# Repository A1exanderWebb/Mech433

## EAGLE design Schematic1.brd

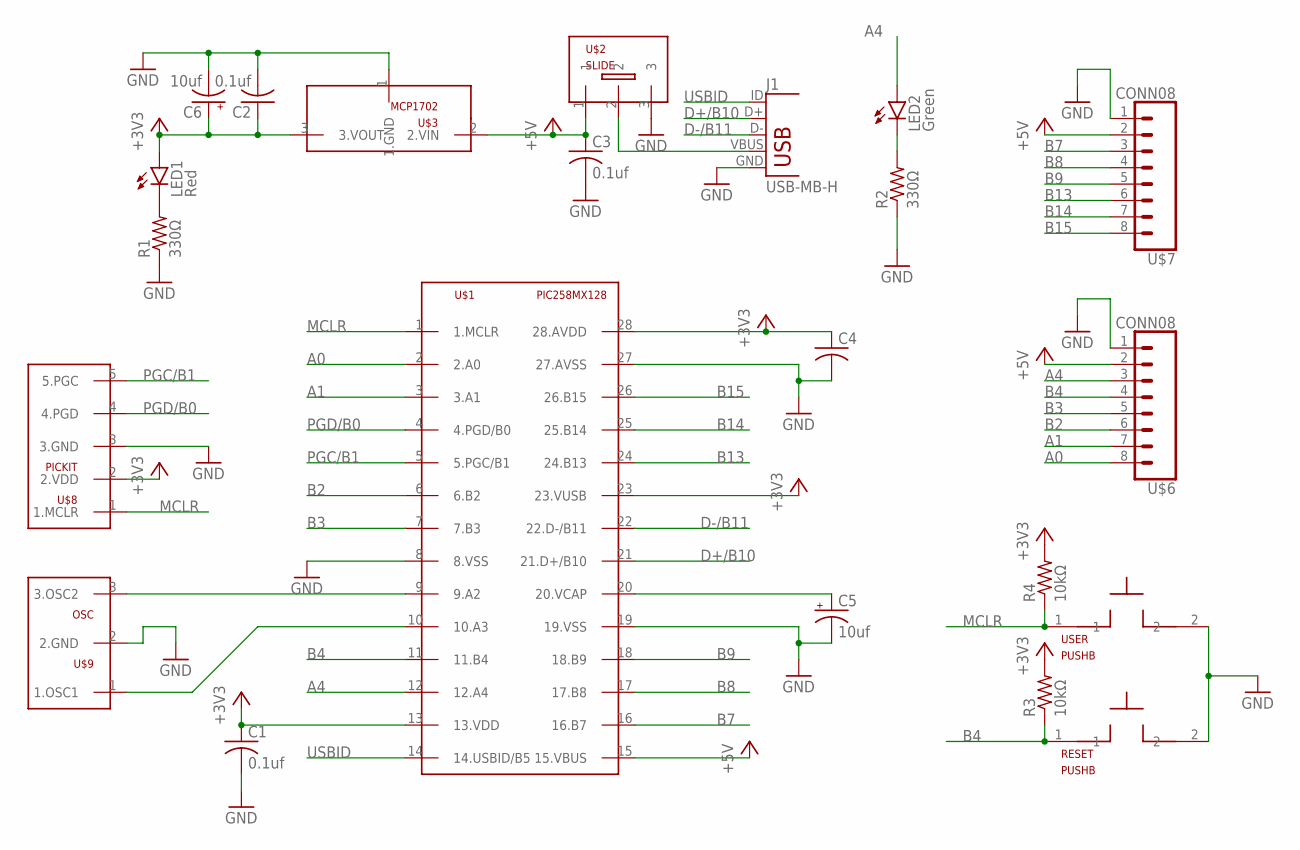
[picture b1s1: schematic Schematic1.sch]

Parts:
C1, C2, C3: 0.1uf; C025-025X050
C4: C-US025-025X050; C025-025X050
C5, C6: 10uf; B45181B
J1: USB-MB-H
LED1: Red; LED3MM
LED2: Green; LED3MM
R1, R2: 330Ω; 0207/10
R3, R4: 10kΩ; 0207/10
RESET: PUSHB
U$1: PIC258MX128; DIL28-3
U$2: SLIDE
U$3: MCP1702; TO92
U$6, U$7: CONN08; 1X08
U$8: PICKIT; 1X05
U$9: OSC
USER: PUSHB

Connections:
+3V3: C1.1, C2.1, C4.1, C6.+, LED1.A, R3.2, R4.2, U$1.13 (13.VDD), U$1.23 (23.VUSB), U$1.28 (28.AVDD), U$3.3 (3.VOUT), U$8.2 (2.VDD)
+5V: C3.1, U$1.15 (15.VBUS), U$2.1, U$3.2 (2.VIN), U$6.2, U$7.2
A0: U$1.2 (2.A0), U$6.8
A1: U$1.3 (3.A1), U$6.7
A4: LED2.A, U$1.12 (12.A4), U$6.3
B2: U$1.6 (6.B2), U$6.6
B3: U$1.7 (7.B3), U$6.5
B4: R3.1, RESET.1, U$1.11 (11.B4), U$6.4
B7: U$1.16 (16.B7), U$7.3
B8: U$1.17 (17.B8), U$7.4
B9: U$1.18 (18.B9), U$7.5
B13: U$1.24 (24.B13), U$7.6
B14: U$1.25 (25.B14), U$7.7
B15: U$1.26 (26.B15), U$7.8
D+/B10: J1.D+, U$1.21 (21.D+/B10)
D-/B11: J1.D-, U$1.22 (22.D-/B11)
GND: C1.2, C2.2, C3.2, C4.2, C5.-, C6.-, J1.GND, R1.1, R2.1, RESET.2, U$1.8 (8.VSS), U$1.19 (19.VSS), U$1.27 (27.AVSS), U$2.3, U$3.1 (1.GND), U$6.1, U$7.1, U$8.3 (3.GND), U$9.2 (2.GND), USER.2
MCLR: R4.1, U$1.1 (1.MCLR), U$8.1 (1.MCLR), USER.1
unnamed: J1.VBUS, U$2.2
unnamed: U$1.9 (9.A2), U$9.3 (3.OSC2)
unnamed: LED1.K (C), R1.2
unnamed: U$1.10 (10.A3), U$9.1 (1.OSC1)
unnamed: C5.+, U$1.20 (20.VCAP)
unnamed: LED2.K (C), R2.2
PGC/B1: U$1.5 (5.PGC/B1), U$8.5 (5.PGC)
PGD/B0: U$1.4 (4.PGD/B0), U$8.4 (4.PGD)
USBID: J1.ID, U$1.14 (14.USBID/B5)

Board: 2 copper layers, 22 parts (0 on the bottom side), 27 nets, no tracks yet.

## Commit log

2019-04-09 Moved items to folder
2019-04-18 Homework 4
2019-04-22 Updated timing oh HW 1
2019-04-22 added fps counter to hw 6
    debatabley does not work.
2019-04-22 Changed colors and timing
2019-04-28 added photo
    to class 4
2019-05-02 Class 5
    no wifi for most of this assignment, first commit=last commit
2019-05-16 Class 8
2019-05-21 Added photos
    Broke everything else
2019-05-24 HW10 up and running
2019-05-24 HW11
2019-05-24 recalculated constants
2019-05-24 Added Cad Files
2019-05-24 Photos
2019-05-28 Homework 12
    mouse works (sometimes)
2019-06-05 Added Plots
2019-06-14 Final Tech cup
